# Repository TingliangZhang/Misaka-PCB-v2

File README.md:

# Misaka-PCB-v2

Second Version of [TingliangZhang](https://github.com/TingliangZhang)/**[Misaka-PCB](https://github.com/TingliangZhang/Misaka-PCB)**

Using [KiCad EDA](https://kicad.org/)

插件安装等参考TUNA的帮助：

https://mirrors.tuna.tsinghua.edu.cn/help/kicad/

## CSV File (BOM)

需要将 ; 批量替换成 , 

## Keyboard commands - hotkeys

Many commands are accessible directly with the keyboard. Selection can be either upper or lower case. Most hot keys are shown in menus. Some hot keys that do not appear are:

- `Delete`: deletes a footprint or a track. (*Available only if the Footprint mode or the Track mode is active*)
- `V`: if the track tool is active switches working layer or place via, if a track is in progress.
- `+` and `-`: select next or previous layer.
- `?`: display the list of all hot keys.
- `Space`: reset relative coordinates.

## Third Party Libraries

In addition to the official KiCad libraries, there are other, third party sources for KiCad library packages.

While the following links may be useful sources of library packages, they are not maintained or endorsed by the KiCad project.

### Digi-Key

[Digi-Key](https://www.digikey.com/) maintains an atomic parts library for KiCad on their [GitHub page](https://github.com/digikey/digikey-kicad-library/). These libraries are licensed under an agreement similar to the official libraries.

### SparkFun

[SparkFun Electronics](https://sparkfun.com/) provide KiCad library files for many of their products on their [GitHub page](https://github.com/sparkfun/SparkFun-KiCad-Libraries). These libraries are based on the SparkFun Eagle libraries.

### SnapEDA

[SnapEDA](https://www.snapeda.com/) provides KiCad symbol and footprint libraries for their customers. The libraries are freely available and can be found on their [KiCad library page](https://www.snapeda.com/kicad). The library license can be found on their [terms of service page](https://www.snapeda.com/about/terms).

### Import Steps For KiCad 5 and Newer

https://www.snapeda.com/

1. In KiCad, go to *Tools > Edit PCB Footprints*.
2. Click on *Preferences > Manage Footprint Libraries*.

#### *For version 5.0*

In the *Global Libraries* tab, click on *Browse Libraries* and navigate to the downloaded folder after unzipping the .zip file. Then click *OK*.

1. Click on *Load footprint from library > Select by Browser*.
2. Navigate to the library folder you imported.
3. Double-click on the footprint to open it.

#### *For version 5.1*

In the *Global Libraries* tab, click on *Add existing library to table*, the small folder icon, and navigate to the downloaded folder after unzipping the .zip file. Then click *OK*.

1. Go to the libraries menu on the left side.
2. Navigate to the library folder you imported.
3. Click on it to open the drop-down menu and double-click on the footprint.

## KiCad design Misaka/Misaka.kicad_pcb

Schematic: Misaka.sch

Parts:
ICSP1: Conn_02x03_Odd_Even; PinHeader_2x03_P2.54mm_Vertical
J1: Conn_Coaxial_Power; AMASS_XT30PW-M_1x02_P2.50mm_Horizontal
MOD1: XB24CZ7PIT-004; XBEE_PRO-20_THT; MPN XB24CZ7PIT-004; Digi-Key_PN 602-1557-ND
R26: 1M; R_0603_1608Metric_Pad1.05x0.95mm_HandSolder
SW1: SW_DIP_x03; SW_DIP_SPSTx03_Slide_6.7x9.18mm_W8.61mm_P2.54mm_LowProfile
U2: ATmega2560-16AU; TQFP-100_14x14mm_P0.5mm
Y1: CSTLS16M0X51-B0; Resonator_muRata_CSTLSxxxX-3Pin_W5.5mm_H3.0mm

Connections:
+3V3: MOD1.1 (Vcc); also elsewhere on the board
+5V: ICSP1.2, SW1.1, SW1.2, SW1.3, U2.10 (VCC), U2.31 (VCC), U2.61 (VCC), U2.80 (VCC), U2.100 (AVCC); also elsewhere on the board
+12V: J1.1; also elsewhere on the board
/D3: U2.7 (PE5); also elsewhere on the board
/D6: U2.15 (PH3); also elsewhere on the board
/D7: U2.16 (PH4); also elsewhere on the board
/D8: U2.17 (PH5); also elsewhere on the board
/D9: U2.18 (PH6); also elsewhere on the board
/D10: U2.23 (PB4); also elsewhere on the board
/D11: U2.24 (PB5); also elsewhere on the board
/D13: U2.26 (PB7); also elsewhere on the board
/MISO: ICSP1.1, U2.22 (PB3)
/MOSI: ICSP1.4, U2.21 (PB2)
/MS1: SW1.6; also elsewhere on the board
/MS2: SW1.5; also elsewhere on the board
/MS3: SW1.4; also elsewhere on the board
/RESET: ICSP1.5, U2.30 (~RESET); also elsewhere on the board
/RX0: U2.2 (PE0); also elsewhere on the board
/RX1: MOD1.2 (DOUT), U2.45 (PD2)
/RX2: U2.12 (PH0); also elsewhere on the board
/SCK: ICSP1.3, U2.20 (PB1)
/SCL: U2.43 (PD0); also elsewhere on the board
/SDA: U2.44 (PD1); also elsewhere on the board
/TX0: U2.3 (PE1); also elsewhere on the board
/TX1: MOD1.3 (DIN/~Config), U2.46 (PD3)
/TX2: U2.13 (PH1); also elsewhere on the board
GND: ICSP1.6, J1.2, MOD1.10 (GND), U2.11 (GND), U2.32 (GND), U2.62 (GND), U2.81 (GND), U2.99 (GND), Y1.2; also elsewhere on the board
unnamed: R26.1, U2.34 (XTAL1), Y1.1
unnamed: R26.2, U2.33 (XTAL2), Y1.3

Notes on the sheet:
Connect with TX1/RX1

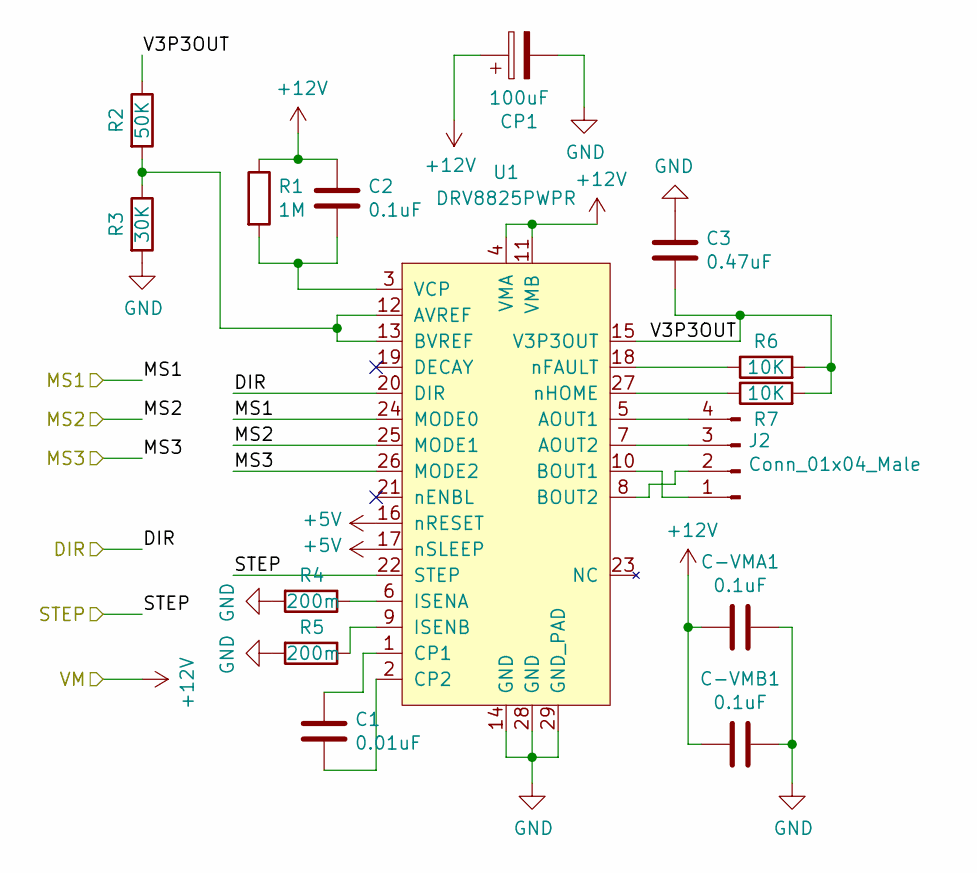
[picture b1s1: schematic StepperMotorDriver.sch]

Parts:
C1: 0.01uF; C_0603_1608Metric_Pad1.05x0.95mm_HandSolder
C2: 0.1uF; C_0603_1608Metric_Pad1.05x0.95mm_HandSolder
C3: 0.47uF; C_0603_1608Metric_Pad1.05x0.95mm_HandSolder
C-VMA1: 0.1uF; C_0603_1608Metric_Pad1.05x0.95mm_HandSolder
C-VMB1: 0.1uF; C_0603_1608Metric_Pad1.05x0.95mm_HandSolder
CP1: 100uF; CP_EIA-3528-21_Kemet-B_Pad1.50x2.35mm_HandSolder
J2: Conn_01x04_Male; Molex_PicoBlade_53047-0410_1x04_P1.25mm_Vertical
R1: 1M; R_0603_1608Metric_Pad1.05x0.95mm_HandSolder
R2: 50K; R_0603_1608Metric_Pad1.05x0.95mm_HandSolder
R3: 30K; R_0603_1608Metric_Pad1.05x0.95mm_HandSolder
R4, R5: 200m; R_0603_1608Metric_Pad1.05x0.95mm_HandSolder
R6, R7: 10K; R_0603_1608Metric_Pad1.05x0.95mm_HandSolder
U1: DRV8825PWPR; HTSSOP-28-1EP_4.4x9.7mm_P0.65mm_EP3.4x9.5mm_ThermalVias

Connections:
+5V: U1.16 (nRESET), U1.17 (nSLEEP); also elsewhere on the board
+12V: C2.1, C-VMA1.2, C-VMB1.2, CP1.1, R1.1, U1.4 (VMA), U1.11 (VMB); also elsewhere on the board
/D6: U1.22 (STEP); also elsewhere on the board
/D7: U1.20 (DIR); also elsewhere on the board
/MS1: U1.24 (MODE0); also elsewhere on the board
/MS2: U1.25 (MODE1); also elsewhere on the board
/MS3: U1.26 (MODE2); also elsewhere on the board
/StepperMotorDriver1/V3P3OUT: C3.2, R2.1, R6.2, R7.2, U1.15 (V3P3OUT)
GND: C3.1, C-VMA1.1, C-VMB1.1, CP1.2, R3.2, R4.2, R5.2, U1.14 (GND), U1.28 (GND), U1.29 (GND_PAD); also elsewhere on the board
unnamed: C1.1, U1.1 (CP1)
unnamed: C1.2, U1.2 (CP2)
unnamed: C2.2, R1.2, U1.3 (VCP)
unnamed: J2.1, U1.10 (BOUT1)
unnamed: J2.2, U1.8 (BOUT2)
unnamed: J2.3, U1.7 (AOUT2)
unnamed: J2.4, U1.5 (AOUT1)
unnamed: R2.2, R3.1, U1.12 (AVREF), U1.13 (BVREF)
unnamed: R4.1, U1.6 (ISENA)
unnamed: R5.1, U1.9 (ISENB)
unnamed: R6.1, U1.18 (nFAULT)
unnamed: R7.1, U1.27 (nHOME)

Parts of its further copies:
C4, C7: 0.01uF; C_0603_1608Metric_Pad1.05x0.95mm_HandSolder
C5, C8: 0.1uF; C_0603_1608Metric_Pad1.05x0.95mm_HandSolder
C6, C9: 0.47uF; C_0603_1608Metric_Pad1.05x0.95mm_HandSolder
C-VMA2, C-VMA3: 0.1uF; C_0603_1608Metric_Pad1.05x0.95mm_HandSolder
C-VMB2, C-VMB3: 0.1uF; C_0603_1608Metric_Pad1.05x0.95mm_HandSolder
CP2, CP3: 100uF; CP_EIA-3528-21_Kemet-B_Pad1.50x2.35mm_HandSolder
J3, J4: Conn_01x04_Male; Molex_PicoBlade_53047-0410_1x04_P1.25mm_Vertical
R8, R15: 50K; R_0603_1608Metric_Pad1.05x0.95mm_HandSolder
R9, R16: 30K; R_0603_1608Metric_Pad1.05x0.95mm_HandSolder
R10, R17: 1M; R_0603_1608Metric_Pad1.05x0.95mm_HandSolder
R11, R12, R18, R19: 200m; R_0603_1608Metric_Pad1.05x0.95mm_HandSolder
R13, R14, R20, R21: 10K; R_0603_1608Metric_Pad1.05x0.95mm_HandSolder
U3, U4: DRV8825PWPR; HTSSOP-28-1EP_4.4x9.7mm_P0.65mm_EP3.4x9.5mm_ThermalVias

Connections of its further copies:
+5V: U3.16 (nRESET), U3.17 (nSLEEP), U4.16 (nRESET), U4.17 (nSLEEP); also elsewhere on the board
+12V: C5.1, C8.1, C-VMA2.2, C-VMA3.2, C-VMB2.2, C-VMB3.2, CP2.1, CP3.1, R10.1, R17.1, U3.4 (VMA), U3.11 (VMB), U4.4 (VMA), U4.11 (VMB); also elsewhere on the board
/D8: U3.22 (STEP); also elsewhere on the board
/D9: U3.20 (DIR); also elsewhere on the board
/D10: U4.22 (STEP); also elsewhere on the board
/D11: U4.20 (DIR); also elsewhere on the board
/MS1: U3.24 (MODE0), U4.24 (MODE0); also elsewhere on the board
/MS2: U3.25 (MODE1), U4.25 (MODE1); also elsewhere on the board
/MS3: U3.26 (MODE2), U4.26 (MODE2); also elsewhere on the board
/StepperMotorDriver2/V3P3OUT: C6.2, R8.1, R13.2, R14.2, U3.15 (V3P3OUT)
/StepperMotorDriver3/V3P3OUT: C9.2, R15.1, R20.2, R21.2, U4.15 (V3P3OUT)
GND: C6.1, C9.1, C-VMA2.1, C-VMA3.1, C-VMB2.1, C-VMB3.1, CP2.2, CP3.2, R9.2, R11.2, R12.2, R16.2, R18.2, R19.2, U3.14 (GND), U3.28 (GND), U3.29 (GND_PAD), U4.14 (GND), U4.28 (GND), U4.29 (GND_PAD); also elsewhere on the board
unnamed: C4.1, U3.1 (CP1)
unnamed: C4.2, U3.2 (CP2)
unnamed: C5.2, R10.2, U3.3 (VCP)
unnamed: C7.1, U4.1 (CP1)
unnamed: C7.2, U4.2 (CP2)
unnamed: C8.2, R17.2, U4.3 (VCP)
unnamed: J3.1, U3.10 (BOUT1)
unnamed: J3.2, U3.8 (BOUT2)
unnamed: J3.3, U3.7 (AOUT2)
unnamed: J3.4, U3.5 (AOUT1)
unnamed: J4.1, U4.10 (BOUT1)
unnamed: J4.2, U4.8 (BOUT2)
unnamed: J4.3, U4.7 (AOUT2)
unnamed: J4.4, U4.5 (AOUT1)
unnamed: R8.2, R9.1, U3.12 (AVREF), U3.13 (BVREF)
unnamed: R11.1, U3.6 (ISENA)
unnamed: R12.1, U3.9 (ISENB)
unnamed: R13.1, U3.18 (nFAULT)
unnamed: R14.1, U3.27 (nHOME)
unnamed: R15.2, R16.1, U4.12 (AVREF), U4.13 (BVREF)
unnamed: R18.1, U4.6 (ISENA)
unnamed: R19.1, U4.9 (ISENB)
unnamed: R20.1, U4.18 (nFAULT)
unnamed: R21.1, U4.27 (nHOME)

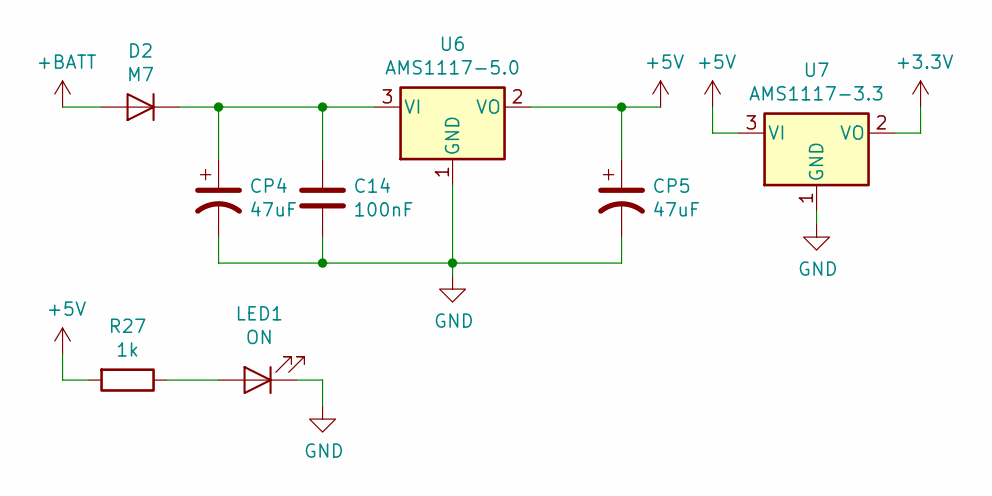
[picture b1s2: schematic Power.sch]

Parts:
C14: 100nF; C_0603_1608Metric_Pad1.05x0.95mm_HandSolder
CP4, CP5: 47uF; CP_Elec_6.3x5.8
D2: M7; D_SMA_Handsoldering
LED1: ON; LED_0603_1608Metric_Pad1.05x0.95mm_HandSolder
R27: 1k; R_0603_1608Metric_Pad1.05x0.95mm_HandSolder
U6: AMS1117-5.0; SOT-223-3_TabPin2
U7: AMS1117-3.3; SOT-223-3_TabPin2

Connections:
+3V3: U7.2 (VO); also elsewhere on the board
+5V: CP5.1, R27.2, U6.2 (VO), U7.3 (VI); also elsewhere on the board
+12V: D2.2 (A); also elsewhere on the board
GND: C14.2, CP4.2, CP5.2, LED1.1 (K), U6.1 (GND), U7.1 (GND); also elsewhere on the board
unnamed: C14.1, CP4.1, D2.1 (K), U6.3 (VI)
unnamed: LED1.2 (A), R27.1

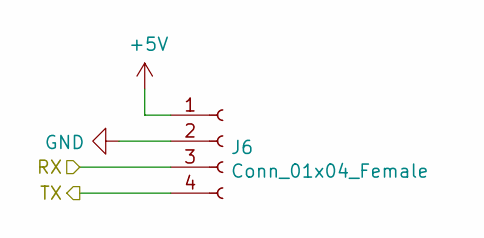
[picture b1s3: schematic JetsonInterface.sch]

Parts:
J6: Conn_01x04_Female; PinHeader_1x04_P2.54mm_Vertical

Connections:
+5V: J6.1; also elsewhere on the board
/RX2: J6.4; also elsewhere on the board
/TX2: J6.3; also elsewhere on the board
GND: J6.2; also elsewhere on the board

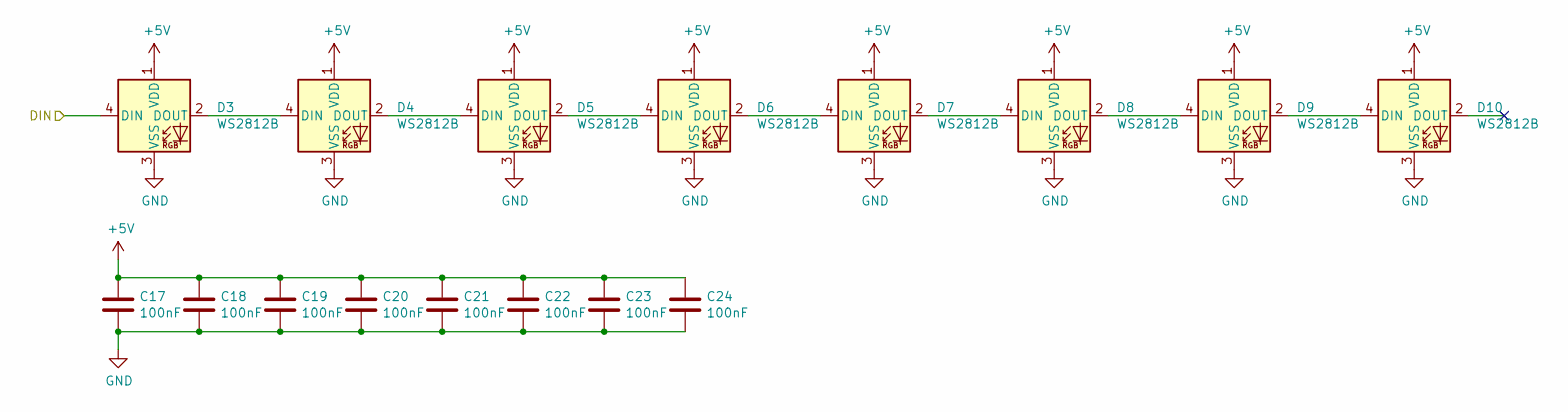
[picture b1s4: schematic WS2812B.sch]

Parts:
C17, C18, C19, C20, C21, C22, C23, C24: 100nF; C_0603_1608Metric_Pad1.05x0.95mm_HandSolder
D3, D4, D5, D6, D7, D8, D9, D10: WS2812B; LED_WS2812B_PLCC4_5.0x5.0mm_P3.2mm

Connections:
+5V: C17.1, C18.1, C19.1, C20.1, C21.1, C22.1, C23.1, C24.1, D3.1 (VDD), D4.1 (VDD), D5.1 (VDD), D6.1 (VDD), D7.1 (VDD), D8.1 (VDD), D9.1 (VDD), D10.1 (VDD); also elsewhere on the board
/D3: D3.4 (DIN); also elsewhere on the board
GND: C17.2, C18.2, C19.2, C20.2, C21.2, C22.2, C23.2, C24.2, D3.3 (VSS), D4.3 (VSS), D5.3 (VSS), D6.3 (VSS), D7.3 (VSS), D8.3 (VSS), D9.3 (VSS), D10.3 (VSS); also elsewhere on the board
unnamed: D3.2 (DOUT), D4.4 (DIN)
unnamed: D4.2 (DOUT), D5.4 (DIN)
unnamed: D5.2 (DOUT), D6.4 (DIN)
unnamed: D6.2 (DOUT), D7.4 (DIN)
unnamed: D7.2 (DOUT), D8.4 (DIN)
unnamed: D8.2 (DOUT), D9.4 (DIN)
unnamed: D9.2 (DOUT), D10.4 (DIN)

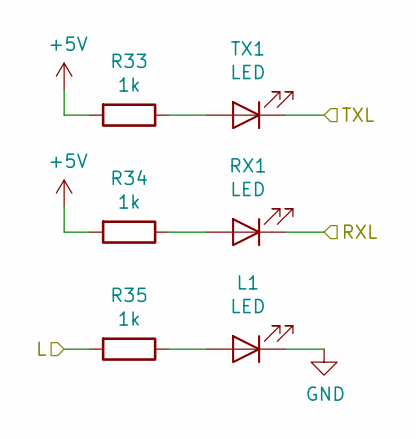
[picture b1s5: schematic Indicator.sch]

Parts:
L1: LED; LED_0603_1608Metric_Pad1.05x0.95mm_HandSolder
R33, R34, R35: 1k; R_0603_1608Metric_Pad1.05x0.95mm_HandSolder
RX1: LED; LED_0603_1608Metric_Pad1.05x0.95mm_HandSolder
TX1: LED; LED_0603_1608Metric_Pad1.05x0.95mm_HandSolder

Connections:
+5V: R33.2, R34.2; also elsewhere on the board
/D13: R35.2; also elsewhere on the board
/RX0: TX1.1 (K); also elsewhere on the board
/TX0: RX1.1 (K); also elsewhere on the board
GND: L1.1 (K); also elsewhere on the board
unnamed: L1.2 (A), R35.1
unnamed: R33.1, TX1.2 (A)
unnamed: R34.1, RX1.2 (A)

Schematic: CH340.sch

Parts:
C10, C11, C12: 100nF; C_0603_1608Metric_Pad1.05x0.95mm_HandSolder
C13: 22pF; C_0603_1608Metric_Pad1.05x0.95mm_HandSolder
D1: CD1206; D_1206_3216Metric_Pad1.42x1.75mm_HandSolder
J5: USB_B_Micro; USB_Micro-B_Wuerth_614105150721_Vertical
J7: Conn_01x04_Female_UART; PinSocket_1x04_P2.54mm_Vertical
R22, R24, R25: 1k; R_0603_1608Metric_Pad1.05x0.95mm_HandSolder
R23: 10k; R_0603_1608Metric_Pad1.05x0.95mm_HandSolder
S1: TACTILE_SWITCH_SMD_4.5MM
U5: CH340C; SOIC-16_3.9x9.9mm_P1.27mm

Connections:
+5V: C11.2, D1.1 (K), J5.1 (VBUS), J7.1, R23.2, U5.16 (VCC); also elsewhere on the board
/RESET: C12.1, C13.2, D1.2 (A), R23.1, S1.2, S1.3; also elsewhere on the board
/RX0: R25.1; also elsewhere on the board
/TX0: R24.1; also elsewhere on the board
GND: C10.2, C11.1, C13.1, J5.5 (GND), J5.6 (Shield), J7.2, R22.2, S1.1, S1.4, U5.1 (GND); also elsewhere on the board
unnamed: C10.1, U5.4 (V3)
unnamed: C12.2, R22.1, U5.13 (~DTR)
unnamed: J5.2 (D-), U5.6 (UD-)
unnamed: J5.3 (D+), U5.5 (UD+)
unnamed: J7.3, R25.2, U5.3 (RXD)
unnamed: J7.4, R24.2, U5.2 (TXD)

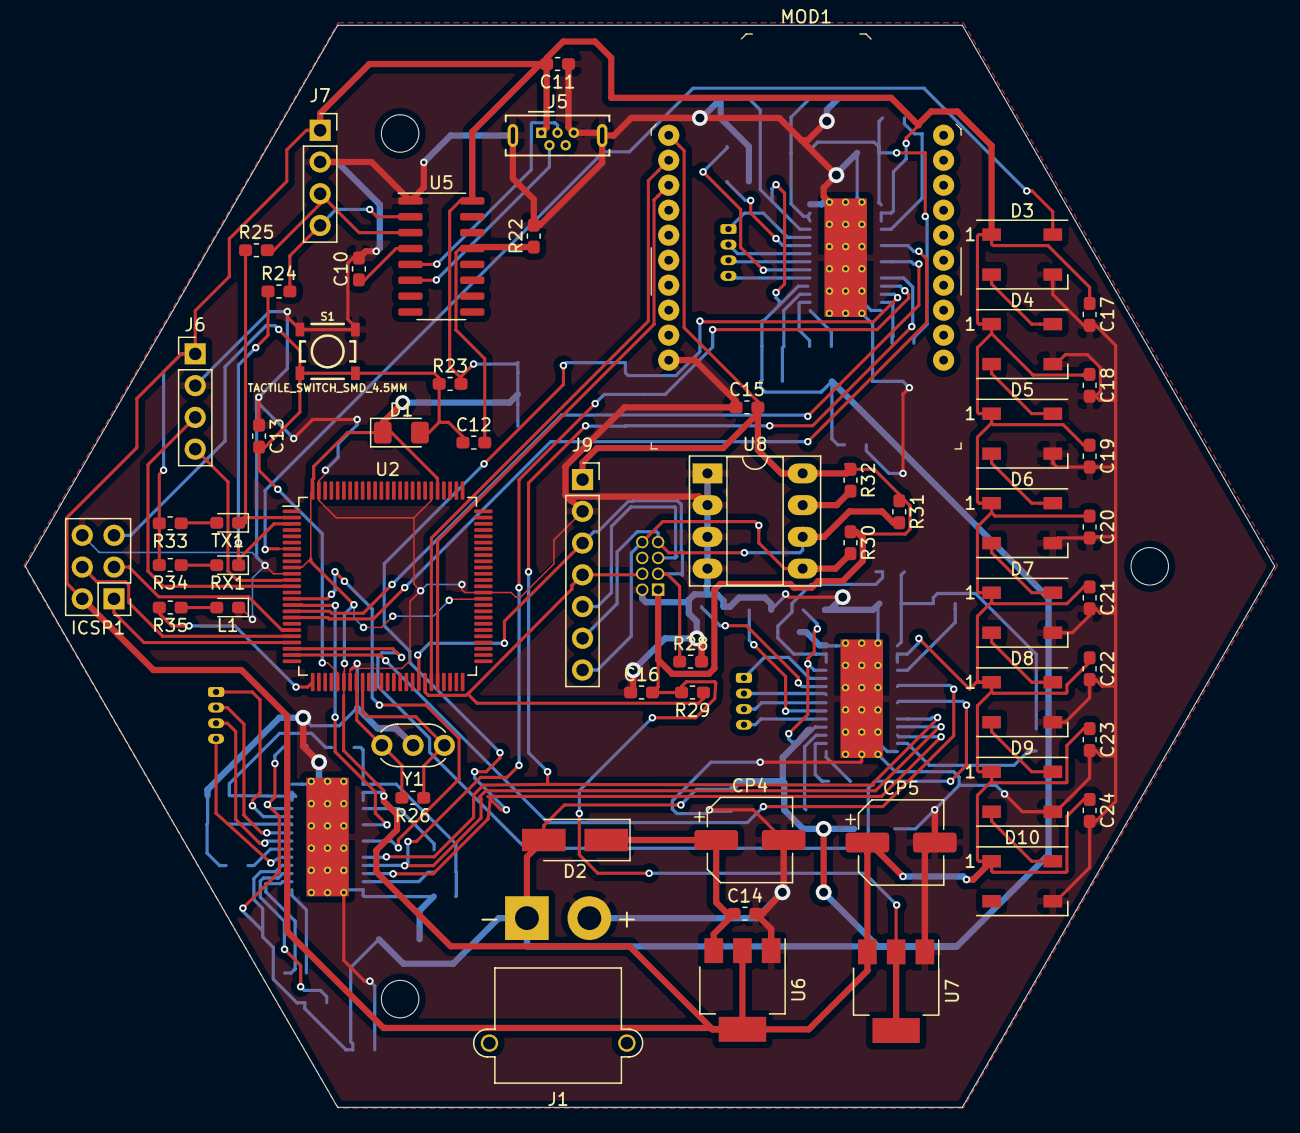
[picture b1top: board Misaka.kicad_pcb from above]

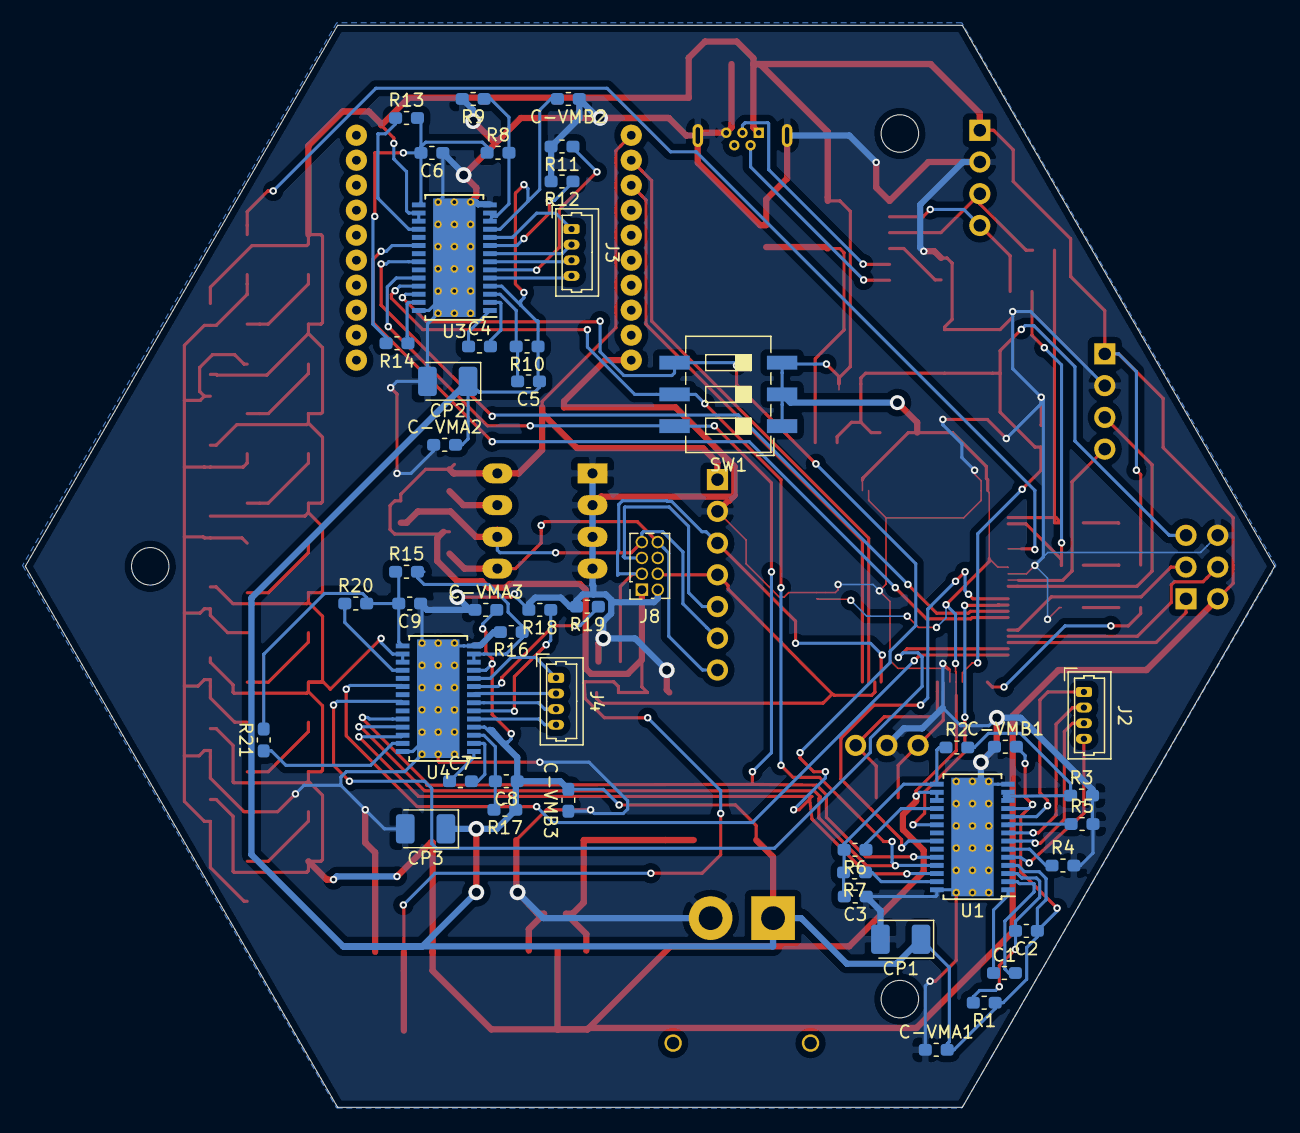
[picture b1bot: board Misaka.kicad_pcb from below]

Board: 2 copper layers, 100.0 x 86.6 mm, 104 parts (47 on the bottom side), 89 nets.

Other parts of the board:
C15, C16: 1uF; C_0603_1608Metric_Pad1.05x0.95mm_HandSolder
J8: Conn_02x04_Odd_Even; PinSocket_2x04_P1.27mm_Vertical
J9: Conn_01x07; PinSocket_1x07_P2.54mm_Vertical
R28: 1k; R_0603_1608Metric_Pad1.05x0.95mm_HandSolder
R29, R30, R31, R32: 4.7k; R_0603_1608Metric_Pad1.05x0.95mm_HandSolder
U8: 24LC02; DIP-8_W7.62mm_Socket_LongPads

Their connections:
+3V3: C15.2, C16.2, J8.1, J9.1, R29.2, R30.1, R31.1, R32.1, U8.8; also elsewhere on the board
/CameraModule/E2PROM-SCK: J8.7, J9.6, R31.2, U8.6
/CameraModule/E2PROM-SDA: J8.8, J9.7, R30.2, U8.5
/CameraModule/EFUSE: J8.5, J9.5
/SCL: J8.3, J9.3, R28.1; also elsewhere on the board
/SDA: J8.4, J9.4, R29.1; also elsewhere on the board
GND: C15.1, C16.1, J8.2, J9.2, R28.2, U8.1, U8.2, U8.3, U8.4; also elsewhere on the board
unnamed: R32.2, U8.7

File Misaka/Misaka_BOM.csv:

"Comment","Description","Designator","Footprint","LibRef","Pins","Quantity","PartNumber","url",
"22pF","desc","C13,","C_0603_1608Metric_Pad1.05x0.95mm_HandSolder","libref","2","1","","",
"1uF","desc","C16,C15,","C_0603_1608Metric_Pad1.05x0.95mm_HandSolder","libref","2","2","","",
"100nF","desc","C24,C23,C22,C21,C20,C19,C18,C17,C14,C12,C11,C10,","C_0603_1608Metric_Pad1.05x0.95mm_HandSolder","libref","2","12","","",
"47uF","desc","CP5,CP4,","CP_Elec_6.3x5.8","libref","2","2","","",
"CD1206","desc","D1,","D_1206_3216Metric_Pad1.42x1.75mm_HandSolder","libref","2","1","","",
"WS2812B","desc","D10,D9,D8,D7,D6,D5,D4,D3,","LED_WS2812B_PLCC4_5.0x5.0mm_P3.2mm","libref","4","8","","",
"M7","desc","D2,","D_SMA_Handsoldering","libref","2","1","","",
"10k","desc","R23,","R_0603_1608Metric_Pad1.05x0.95mm_HandSolder","libref","2","1","","",
"1M","desc","R26,","R_0603_1608Metric_Pad1.05x0.95mm_HandSolder","libref","2","1","","",
"4.7k","desc","R32,R31,R30,R29,","R_0603_1608Metric_Pad1.05x0.95mm_HandSolder","libref","2","4","","",
"1k","desc","R35,R34,R33,R28,R25,R24,R22,","R_0603_1608Metric_Pad1.05x0.95mm_HandSolder","libref","2","7","","",
"TACTILE_SWITCH_SMD_4.5MM","desc","S1,","TACTILE_SWITCH_SMD_4.5MM","libref","4","1","","",
"LED","desc","TX1,RX1,L1,","LED_0603_1608Metric_Pad1.05x0.95mm_HandSolder","libref","2","3","","",
"ATmega2560-16AU","desc","U2,","TQFP-100_14x14mm_P0.5mm","libref","100","1","","",
"CH340C","desc","U5,","SOIC-16_3.9x9.9mm_P1.27mm","libref","16","1","","",
"AMS1117-5.0","desc","U6,","SOT-223-3_TabPin2","libref","4","1","","",
"AMS1117-3.3","desc","U7,","SOT-223-3_TabPin2","libref","4","1","","",
"0.1uF","desc","C-VMB3,C-VMB2,C-VMB1,C-VMA3,C-VMA2,C-VMA1,C8,C5,C2,","C_0603_1608Metric_Pad1.05x0.95mm_HandSolder","libref","2","9","","",
"0.01uF","desc","C7,C4,C1,","C_0603_1608Metric_Pad1.05x0.95mm_HandSolder","libref","2","3","","",
"0.47uF","desc","C9,C6,C3,","C_0603_1608Metric_Pad1.05x0.95mm_HandSolder","libref","2","3","","",
"100uF","desc","CP3,CP2,CP1,","CP_EIA-3528-21_Kemet-B_Pad1.50x2.35mm_HandSolder","libref","2","3","","",
"50K","desc","R15,R8,R2,","R_0603_1608Metric_Pad1.05x0.95mm_HandSolder","libref","2","3","","",
"30K","desc","R16,R9,R3,","R_0603_1608Metric_Pad1.05x0.95mm_HandSolder","libref","2","3","","",
"1M","desc","R17,R10,R1,","R_0603_1608Metric_Pad1.05x0.95mm_HandSolder","libref","2","3","","",
"10K","desc","R21,R20,R14,R13,R7,R6,","R_0603_1608Metric_Pad1.05x0.95mm_HandSolder","libref","2","6","","",
"200m","desc","R4,R19,R18,R12,R11,R5,","R_0603_1608Metric_Pad1.05x0.95mm_HandSolder","libref","2","6","","",
"SW_DIP_x03","desc","SW1,","SW_DIP_SPSTx03_Slide_6.7x9.18mm_W8.61mm_P2.54mm_LowProfile","libref","6","1","","",
"Through Hole Items ",
"Conn_02x03_Odd_Even","desc","ICSP1,","PinHeader_2x03_P2.54mm_Vertical","libref","6","1","","",
"Conn_Coaxial_Power","desc","J1,","AMASS_XT30PW-M_1x02_P2.50mm_Horizontal","libref","4","1","","",
"USB_B_Micro","desc","J5,","USB_Micro-B_Wuerth_614105150721_Vertical","libref","7","1","","",
"Conn_01x04_Female","desc","J6,","PinHeader_1x04_P2.54mm_Vertical","libref","4","1","","",
"Conn_01x04_Female_UART","desc","J7,","PinSocket_1x04_P2.54mm_Vertical","libref","4","1","","",
"Conn_01x07","desc","J9,","PinSocket_1x07_P2.54mm_Vertical","libref","7","1","","",
"XB24CZ7PIT-004","desc","MOD1,","XBEE_PRO-20_THT","libref","20","1","","",
"24LC02","desc","U8,","DIP-8_W7.62mm_Socket_LongPads","libref","8","1","","",
"CSTLS16M0X51-B0","desc","Y1,","Resonator_muRata_CSTLSxxxX-3Pin_W5.5mm_H3.0mm","libref","3","1","","",
"Conn_01x04_Male","desc","J4,J3,J2,","Molex_PicoBlade_53047-0410_1x04_P1.25mm_Vertical","libref","4","3","","",
"Conn_02x04_Odd_Even","desc","J8,","PinSocket_2x04_P1.27mm_Vertical","libref","8","1","","",
"DRV8825PWPR","desc","U4,U3,U1,","HTSSOP-28-1EP_4.4x9.7mm_P0.65mm_EP3.4x9.5mm_ThermalVias","libref","58","3","","",

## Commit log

2020-02-29 Ini DRV8825
2020-03-01 DRV8825
2020-03-01 ROUTE DRV8825
2020-03-01 FINISH DRV8825
2020-03-01 FINISH AGAIN
2020-03-02 Test
2020-03-03 ADD Lib
2020-03-03 redo
2020-03-03 ADD Libraries
2020-03-03 DRV8825-Digi-Key-Lib
2020-03-03 Hierarchical
2020-03-04 Misaka ini
2020-03-05 mega-2560-pro-embed-ch340g-atmega2560-16au
2020-03-05 CH340
2020-03-05 CH340C
2020-03-05 MURATA的 CSTLS16M0X51-A0
2020-03-05 route v1.0
2020-03-05 route v1.1
2020-03-05 Begin Free Routing
2020-03-05 Free Routing
2020-03-06 route v1.3
2020-03-06 change footprint to handsolding
2020-03-06 route v2.0
2020-03-06 route v2.1
2020-03-06 Change Footprint
2020-03-06 route v2.2
2020-03-06 v2 finish
2020-03-06 Gerber
2020-03-07 Render
2020-03-08 KiCad EDA 生产文件生成器
    https://github.com/xtoolbox/kicad_tools
2020-03-08 Kicost
2020-03-23 电池正负极反了
2020-03-29 5V-problem
2020-03-29 v2Gerber
2020-03-29 save
2020-04-23 Update fp-info-cache
2021-11-10 Update README.md
    https://forum.kicad.info/t/warning-avoid-all-links-to-kicad-pcb-org-use-kicad-org/31521
